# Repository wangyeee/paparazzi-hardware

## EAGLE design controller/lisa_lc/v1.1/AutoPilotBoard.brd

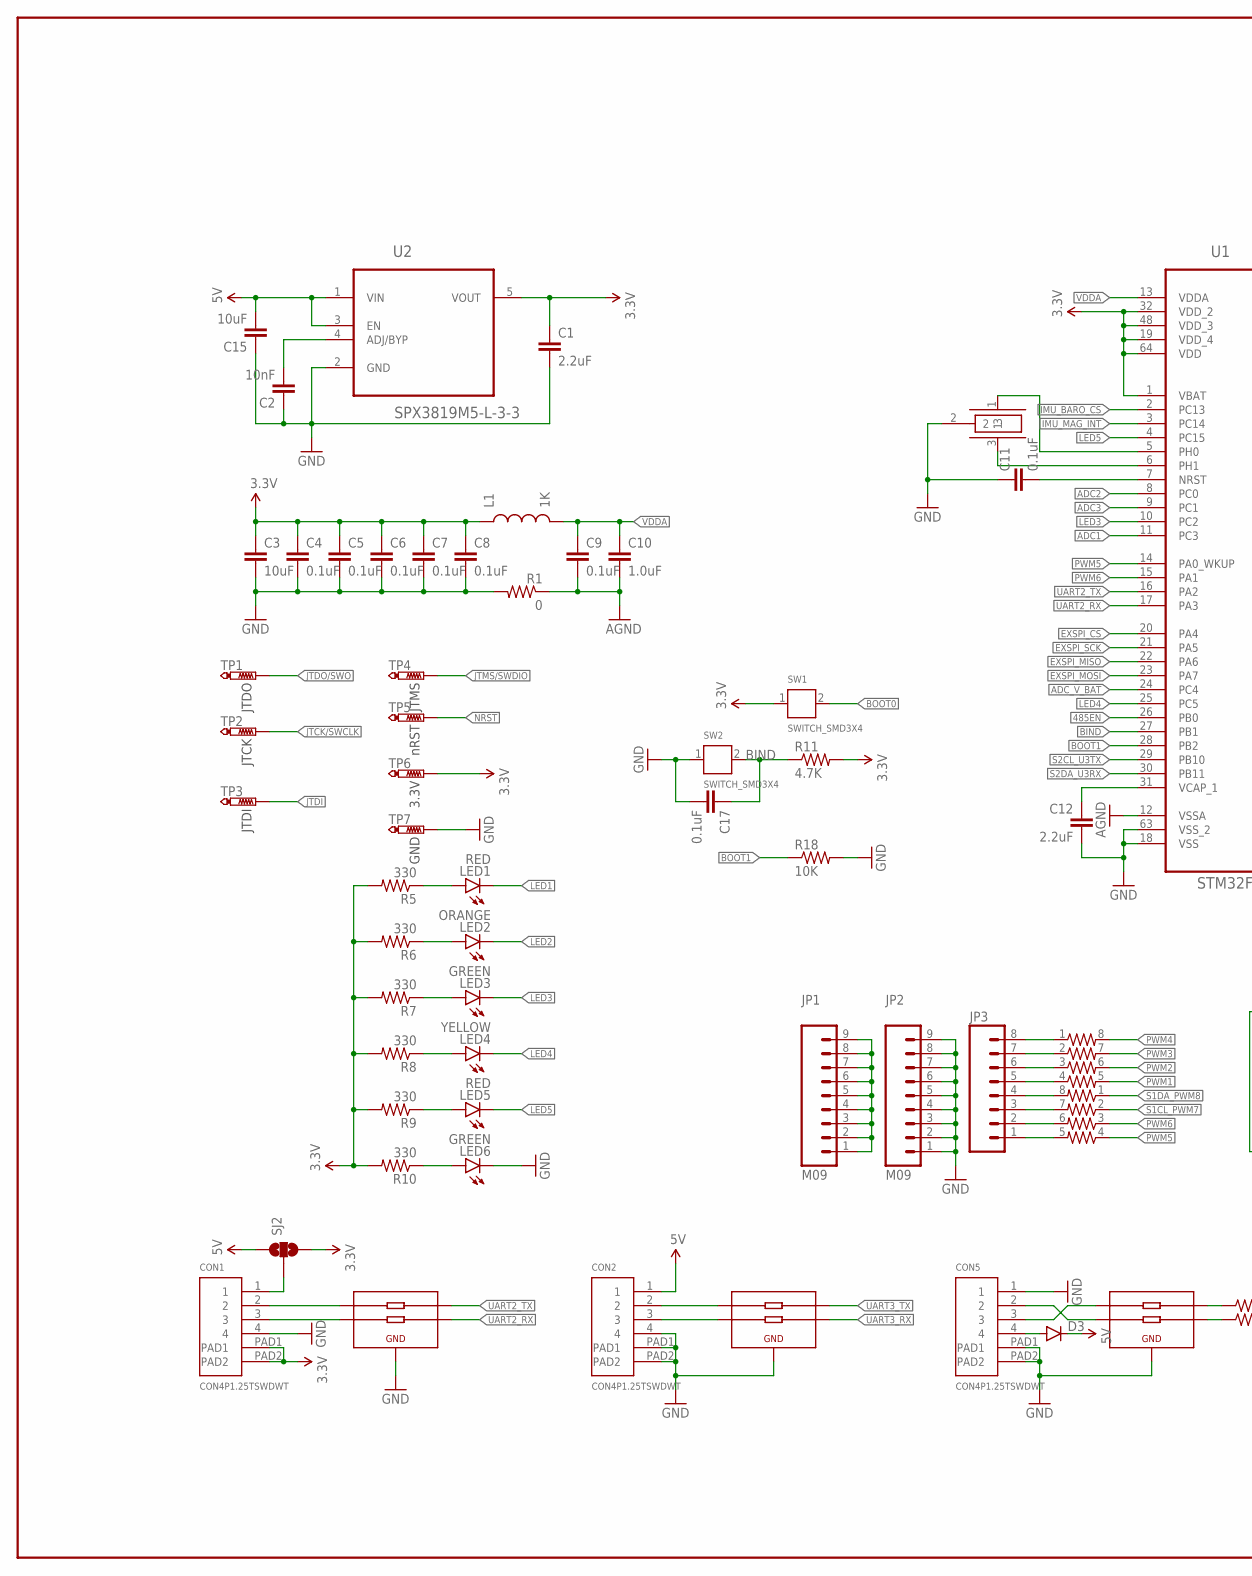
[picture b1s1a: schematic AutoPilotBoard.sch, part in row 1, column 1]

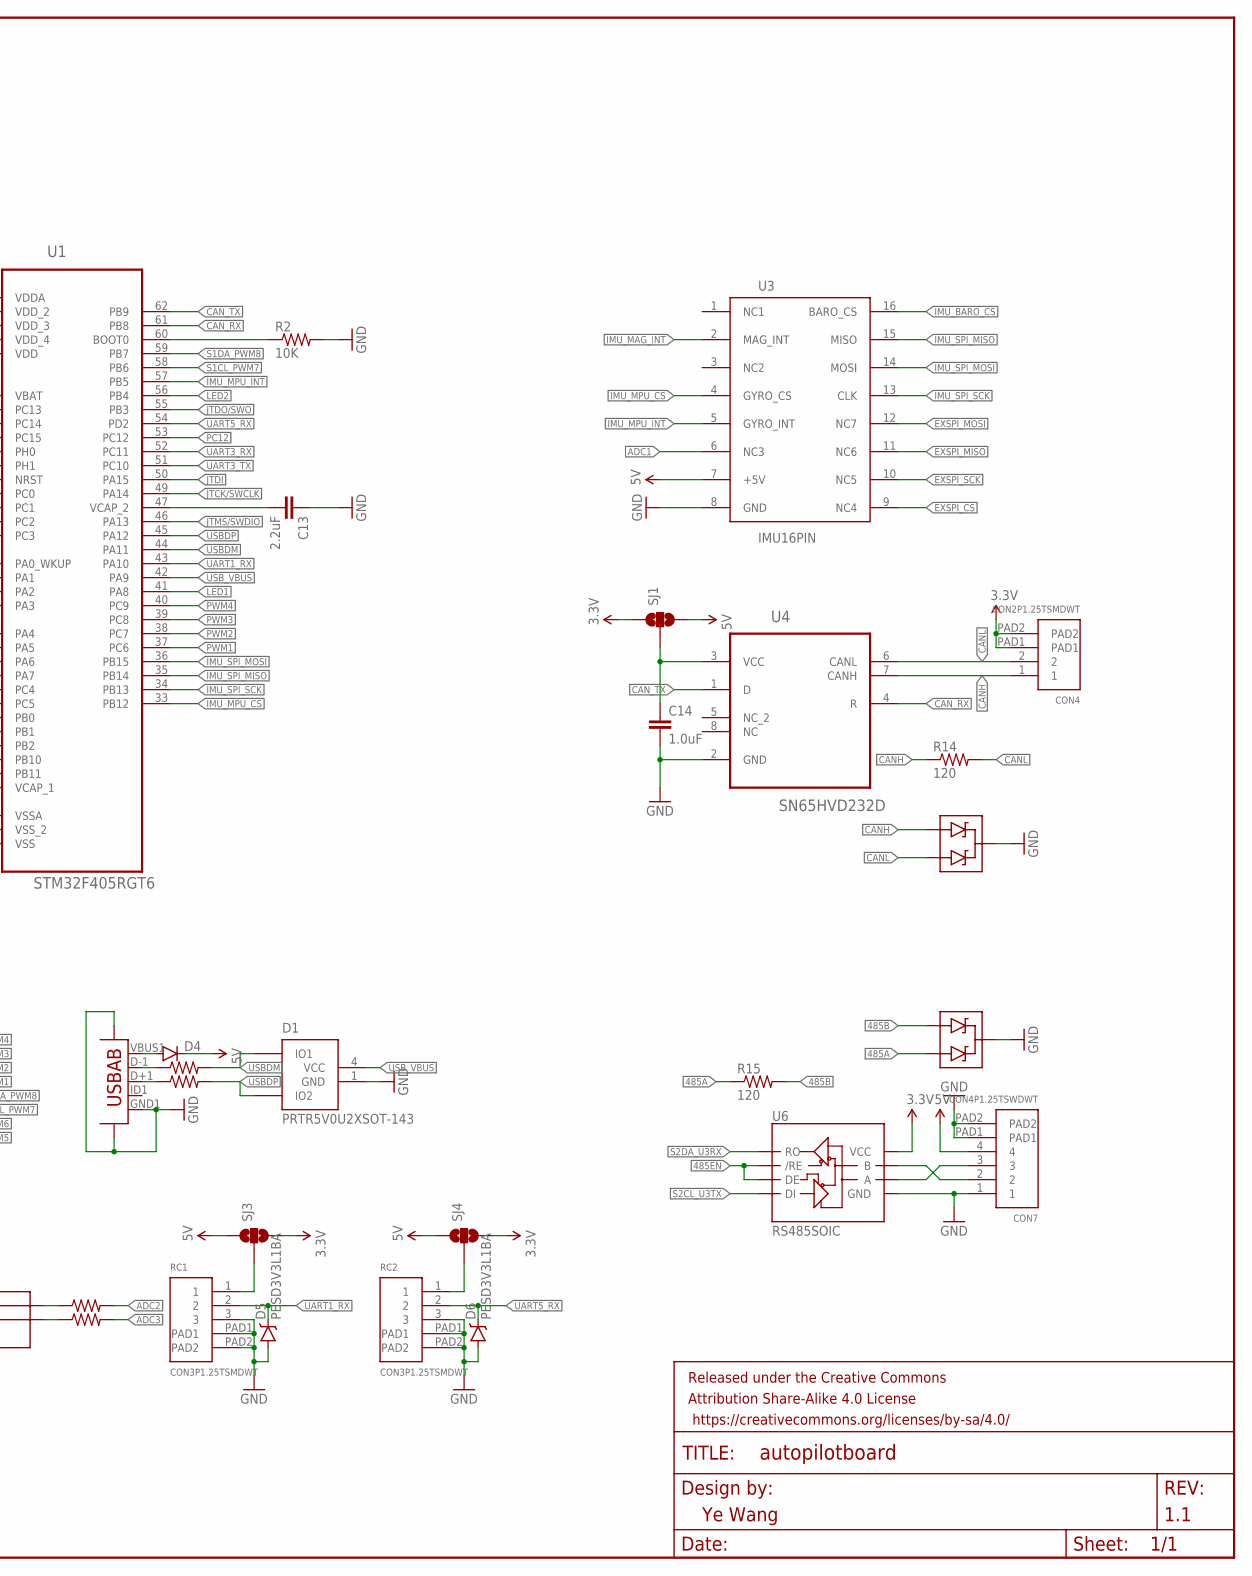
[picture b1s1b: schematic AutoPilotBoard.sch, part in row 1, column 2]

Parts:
C1, C12, C13: 2.2uF; 0603-CAP
C2: 10nF; 0603-CAP
C3: 10uF; 0805-CAP
C4, C5, C6, C7, C8, C9, C11, C17: 0.1uF; 0603-CAP
C10, C14: 1.0uF; 0603-CAP
C15: 10uF; 1206
CON1, CON2, CON5, CON7: CON4P1.25TSWDWT; 1.25T4P
CON4: CON2P1.25TSMDWT; 1.25T2P
D1: PRTR5V0U2XSOT-143; SOT-143B
D2: PESD1CAN; SOT23-3
D3, D4: DIODESOD123; SOD-123
D5, D6: PESD3V3L1BA; SOD-323
D7: SM712; SOT23-3
FIL1, FIL2, FIL3: IP4256CZ5-W; SOT65P210X110-5N
FRAME1: FRAME-LEDGERNO_PKG; DUMMY
JP1, JP2: M09; 1X09
JP3: M08RND; 1X08_ROUND
L1: 1K; 0603
LED1, LED5: RED; LED-0603
LED2: ORANGE; LED-0603
LED3, LED6: GREEN; LED-0603
LED4: YELLOW; LED-0603
R1: 0; 0603-RES
R2, R18: 10K; 0603-RES
R3, R4: 22; 0603-RES
R5, R6, R7, R8, R9, R10: 330; 0603-RES
R11: 4.7K; 0603-RES
R12, R13: 1K; 0603-ARV
R14, R15: 120; 0603-RES
R16, R17: 1K; 0603-RES
RC1, RC2: CON3P1.25TSMDWT; 1.25T3P
SJ1, SJ2, SJ3, SJ4: SOLDERJUMPER_2WAYS; SJ_3
SW1, SW2: SWITCH_SMD3X4; SWITCH3X4_SMD
TP1, TP2, TP3, TP4, TP5, TP6, TP7: PTR1B1,27; B1,27
U1: STM32F405RGT6; QFP50P1200X1200X160-64N
U2: SPX3819M5-L-3-3; SOT95P280X145-5N
U3: IMU16PIN; SMD23X23
U4: SN65HVD232D; SOIC127P600X175-8N
U5: USB-ABCONN-11794; USB-AB-MICRO-SMD_V03
U6: RS485SOIC; SO08
X1: CSTCE8M00G52-R0; CSTCE_M_G

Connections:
3.3V: C1.1, C3.P$1 (1), C4.1, C5.1, C6.1, C7.1, C8.1, CON1.PAD1, CON1.PAD2, CON4.PAD1, CON4.PAD2, L1.1, R5.2, R6.2, R7.2, R8.2, R9.2, R10.2, R11.2, SJ1.1, SJ2.3, SJ3.3, SJ4.3, SW1.1, TP6.TP, U1.1 (VBAT), U1.19 (VDD_4), U1.32 (VDD_2), U1.48 (VDD_3), U1.64 (VDD), U2.5 (VOUT), U6.8 (VCC)
5V: C15.2, CON2.1, CON7.4, D3.C, D4.C, SJ1.3, SJ2.1, SJ3.1, SJ4.1, U2.1 (VIN), U2.3 (EN), U3.7 (+5V)
485A: CON7.3, D7.2 (A2), R15.1, U6.6 (A)
485B: CON7.2, D7.1 (A1), R15.2, U6.7 (B)
485EN: U1.26 (PB0), U6.2 (/RE), U6.3 (DE)
ADC1: U1.11 (PC3), U3.6 (NC3)
ADC2: R16.2, U1.8 (PC0)
ADC3: R17.2, U1.9 (PC1)
ADC_V_BAT: U1.24 (PC4)
AGND: C9.2, C10.2, R1.1, U1.12 (VSSA)
BIND: C17.1, R11.1, SW2.2, U1.27 (PB1)
BOOT0: R2.1, SW1.2, U1.60 (BOOT0)
BOOT1: R18.1, U1.28 (PB2)
CANH: CON4.1, D2.1 (A1), R14.1, U4.7 (CANH)
CANL: CON4.2, D2.2 (A2), R14.2, U4.6 (CANL)
CAN_RX: U1.61 (PB8), U4.4 (R)
CAN_TX: U1.62 (PB9), U4.1 (D)
EXSPI_CS: U1.20 (PA4), U3.9 (NC4)
EXSPI_MISO: U1.22 (PA6), U3.11 (NC6)
EXSPI_MOSI: U1.23 (PA7), U3.12 (NC7)
EXSPI_SCK: U1.21 (PA5), U3.10 (NC5)
GND: C1.2, C2.1, C3.P$2 (2), C4.2, C5.2, C6.2, C7.2, C8.2, C11.1, C12.2, C13.1, C14.2, C15.1, C17.2, CON1.4, CON2.4, CON2.PAD1, CON2.PAD2, CON5.1, CON5.PAD1, CON5.PAD2, CON7.1, CON7.PAD1, CON7.PAD2, D1.1 (GND), D2.3 (C), D5.A, D6.A, D7.3 (C), FIL1.2, FIL2.2, FIL3.2, JP2.1, JP2.2, JP2.3, JP2.4, JP2.5, JP2.6, JP2.7, JP2.8, JP2.9, LED6.C, R1.2, R2.2, R18.2, RC1.3, RC1.PAD1, RC1.PAD2, RC2.3, RC2.PAD1, RC2.PAD2, SW2.1, TP7.TP, U1.18 (VSS), U1.63 (VSS_2), U2.2 (GND), U3.8 (GND), U4.2 (GND), U5.CON1 (SHL1), U5.CON2 (SHL2), U5.GND1 (GND), U6.5 (GND), X1.2
IMU_BARO_CS: U1.2 (PC13), U3.16 (BARO_CS)
IMU_MAG_INT: U1.3 (PC14), U3.2 (MAG_INT)
IMU_MPU_CS: U1.33 (PB12), U3.4 (GYRO_CS)
IMU_MPU_INT: U1.57 (PB5), U3.5 (GYRO_INT)
IMU_SPI_MISO: U1.35 (PB14), U3.15 (MISO)
IMU_SPI_MOSI: U1.36 (PB15), U3.14 (MOSI)
IMU_SPI_SCK: U1.34 (PB13), U3.13 (CLK)
JTCK/SWCLK: TP2.TP, U1.49 (PA14)
JTDI: TP3.TP, U1.50 (PA15)
JTDO/SWO: TP1.TP, U1.55 (PB3)
JTMS/SWDIO: TP4.TP, U1.46 (PA13)
LED1: LED1.C, U1.41 (PA8)
LED2: LED2.C, U1.56 (PB4)
LED3: LED3.C, U1.10 (PC2)
LED4: LED4.C, U1.25 (PC5)
LED5: LED5.C, U1.4 (PC15)
unnamed: C14.1, SJ1.2, U4.3 (VCC)
unnamed: U1.6 (PH1), X1.3
unnamed: C2.2, U2.4 (ADJ/BYP)
unnamed: U1.5 (PH0), X1.1
unnamed: C12.1, U1.31 (VCAP_1)
unnamed: C13.2, U1.47 (VCAP_2)
unnamed: R3.1, U5.D-1 (D-)
unnamed: R4.1, U5.D+1 (D+)
unnamed: LED1.A, R5.1
unnamed: LED3.A, R7.1
unnamed: LED4.A, R8.1
unnamed: LED5.A, R9.1
unnamed: LED2.A, R6.1
unnamed: CON5.3, FIL1.1
unnamed: RC1.1, SJ3.2
unnamed: CON5.2, FIL1.3
unnamed: JP3.5, R12.4 (1)
unnamed: JP3.6, R12.3 (1)
unnamed: JP3.7, R12.2 (1)
unnamed: JP3.8, R12.1
unnamed: JP3.4, R13.8 (2)
unnamed: JP3.3, R13.7 (2)
unnamed: JP3.2, R13.6 (2)
unnamed: LED6.A, R10.1
unnamed: JP3.1, R13.5 (2)
unnamed: FIL1.5, R16.1
unnamed: FIL1.4, R17.1
unnamed: CON1.2, FIL2.1
unnamed: CON1.3, FIL2.3
unnamed: CON2.3, FIL3.4
unnamed: CON2.2, FIL3.5
unnamed: CON5.4, D3.A
unnamed: CON1.1, SJ2.2
unnamed: RC2.1, SJ4.2
NRST: C11.2, TP5.TP, U1.7 (NRST)
PC12: U1.53 (PC12)
PWM1: R12.5 (2), U1.37 (PC6)
PWM2: R12.6 (2), U1.38 (PC7)
PWM3: R12.7 (2), U1.39 (PC8)
PWM4: R12.8 (2), U1.40 (PC9)
PWM5: R13.4 (1), U1.14 (PA0_WKUP)
PWM6: R13.3 (1), U1.15 (PA1)
S1CL_PWM7: R13.2 (1), U1.58 (PB6)
S1DA_PWM8: R13.1, U1.59 (PB7)
S2CL_U3TX: U1.29 (PB10), U6.4 (DI)
S2DA_U3RX: U1.30 (PB11), U6.1 (RO)
SRV_COM: JP1.1, JP1.2, JP1.3, JP1.4, JP1.5, JP1.6, JP1.7, JP1.8, JP1.9
UART1_RX: D5.C, RC1.2, U1.43 (PA10)
UART2_RX: FIL2.4, U1.17 (PA3)
UART2_TX: FIL2.5, U1.16 (PA2)
UART3_RX: FIL3.3, U1.52 (PC11)
UART3_TX: FIL3.1, U1.51 (PC10)
UART5_RX: D6.C, RC2.2, U1.54 (PD2)
USBDM: D1.2 (IO1), R3.2, U1.44 (PA11)
USBDP: D1.3 (IO2), R4.2, U1.45 (PA12)
USB_VBUS: D1.4 (VCC), D4.A, U1.42 (PA9), U5.VBUS1 (VBUS)
VDDA: C9.1, C10.1, L1.2, U1.13 (VDDA)

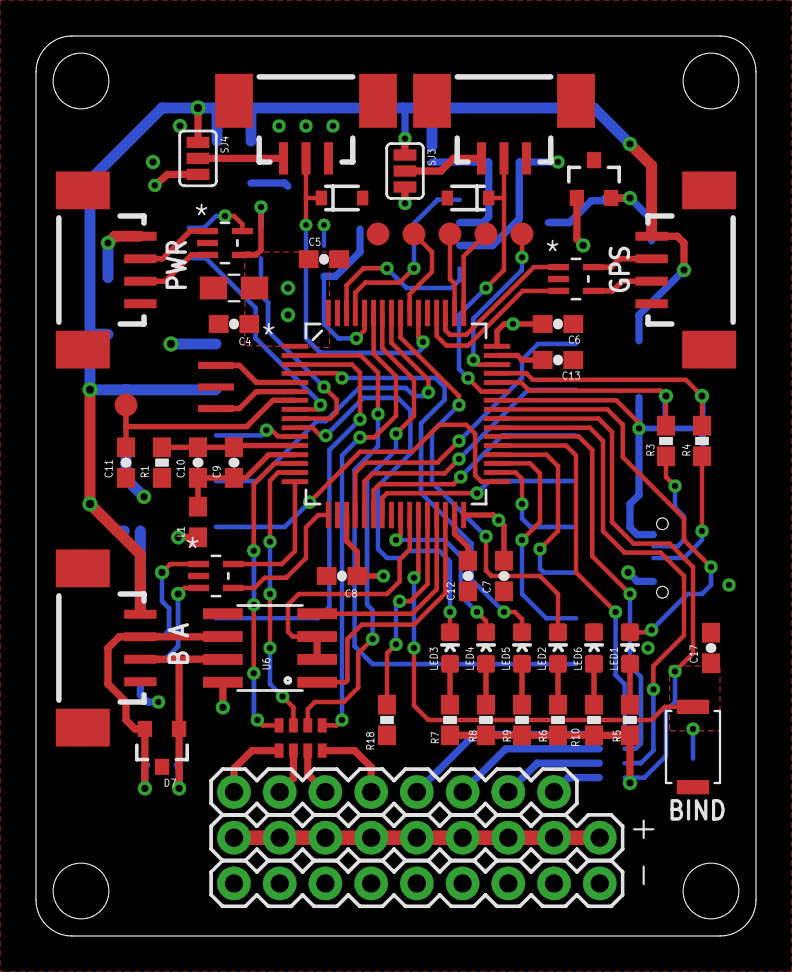
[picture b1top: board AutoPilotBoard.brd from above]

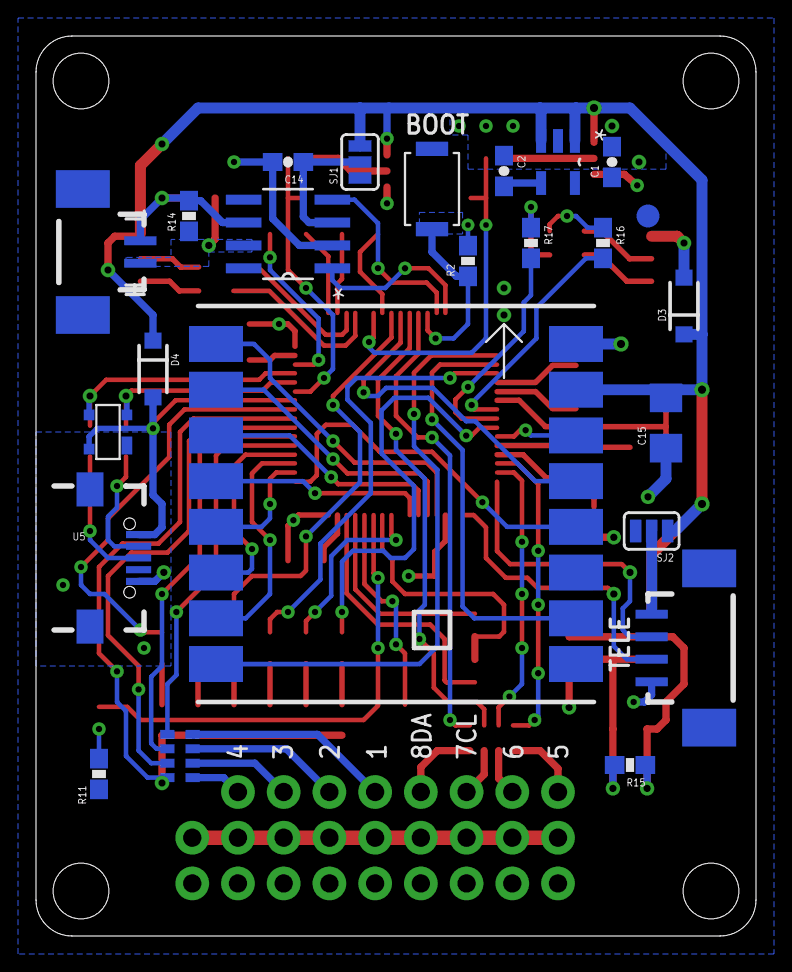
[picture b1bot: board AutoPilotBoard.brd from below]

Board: 2 copper layers, 40.0 x 50.0 mm, 82 parts (24 on the bottom side), 93 nets.

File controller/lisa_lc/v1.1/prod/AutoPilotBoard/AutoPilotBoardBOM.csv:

Part,Value,Package,Description
C1,2.2uF,0603-CAP,Capacitor
C10,1.0uF,0603-CAP,Capacitor
C11,0.1uF,0603-CAP,Capacitor
C12,2.2uF,0603-CAP,Capacitor
C13,2.2uF,0603-CAP,Capacitor
C14,1.0uF,0603-CAP,Capacitor
C15,10uF,1206-CAP,Capacitor
C17,0.1uF,0603-CAP,Capacitor
C2,10nF,0603-CAP,Capacitor
C3,10uF,0805-CAP,Capacitor
C4,0.1uF,0603-CAP,Capacitor
C5,0.1uF,0603-CAP,Capacitor
C6,0.1uF,0603-CAP,Capacitor
C7,0.1uF,0603-CAP,Capacitor
C8,0.1uF,0603-CAP,Capacitor
C9,0.1uF,0603-CAP,Capacitor
CON1,CON4P1.25TSWDWT,1.25T4P,4 Pin 1.25mm SMD Connector
CON2,CON4P1.25TSWDWT,1.25T4P,4 Pin 1.25mm SMD Connector
CON4,CON2P1.25TSMDWT,1.25T2P,4 Pin 1.25mm SMD Connector
CON5,CON4P1.25TSWDWT,1.25T4P,4 Pin 1.25mm SMD Connector
CON7,CON4P1.25TSWDWT,1.25T4P,4 Pin 1.25mm SMD Connector
D1,PRTR5V0U2XSOT-143,SOT-143B,I2C Bus ESD Protection
D2,PESD1CAN,SOT23-3,CAN Bus ESD Protection
D3,MBR0520LT1G,SOD-123,Diode
D4,MBR0520LT1G,SOD-123,Diode
D5,PESD3V3L1BA,SOD-323,Schottky diodes in SFE's production catalog
D6,PESD3V3L1BA,SOD-323,Schottky diodes in SFE's production catalog
D7,SM712,SOT23-3,RS485 Bus ESD protection
FIL1,IP4256CZ5-W,SOT65P210X110-5N,Dual-channel passive filter network with ESD protection
FIL2,IP4256CZ5-W,SOT65P210X110-5N,Dual-channel passive filter network with ESD protection
FIL3,IP4256CZ5-W,SOT65P210X110-5N,Dual-channel passive filter network with ESD protection
JP1,M09,1X09,Header 9
JP2,M09,1X09,Header 9
JP3,M08,1X08_ROUND,Header 8
L1,1K,0603,Inductors
LED1,RED,LED-0603,LED
LED2,ORANGE,LED-0603,LED
LED3,GREEN,LED-0603,LED
LED4,YELLOW,LED-0603,LED
LED5,RED,LED-0603,LED
LED6,GREEN,LED-0603,LED
R1,0,0603-RES,Resistor
R10,330,0603-RES,Resistor
R11,4.7K,0603-RES,Resistor
R12,1K,0603-ARV,Array Chip Resistor
R13,1K,0603-ARV,Array Chip Resistor
R14,120,0603-RES,Resistor
R15,120,0603-RES,Resistor
R16,1K,0603-RES,Resistor
R17,1K,0603-RES,Resistor
R18,10K,0603-RES,Resistor
R2,10K,0603-RES,Resistor
R3,22,0603-RES,Resistor
R4,22,0603-RES,Resistor
R5,330,0603-RES,Resistor
R6,330,0603-RES,Resistor
R7,330,0603-RES,Resistor
R8,330,0603-RES,Resistor
R9,330,0603-RES,Resistor
RC1,CON3P1.25TSMDWT,1.25T3P,3 Pin 1.25mm SMD Connector
RC2,CON3P1.25TSMDWT,1.25T3P,3 Pin 1.25mm SMD Connector
SW1,SWITCH_SMD3X4,SWITCH3X4_SMD,Boot button
SW2,SWITCH_SMD3X4,SWITCH3X4_SMD,Bind button
U1,STM32F405RGT6,LQFP-64PIN,"ARM Cortex M4 MCU with 1MB FLASH, FPU"
U2,SPX3819M5-L-3-3,SOT95P280X145-5N,"500mA, LOW-NOISE LDO VOLTAGE REGULATOR"
U3,IMU16PIN,SMD23X23,IMU
U4,SN65HVD232D,SOIC127P600X175-8N,CAN transceiver
U5,USB-AB CONN,USB-AB-MICRO-SMD_V03,USB AB connector compatible with USB OTG.
U6,RS485SOIC,SOIC8,RS485 transceiver
X1,CSTCE12M0G55-R0,CSTCE_M_G,12MHz resonators with built-in load capacitors.

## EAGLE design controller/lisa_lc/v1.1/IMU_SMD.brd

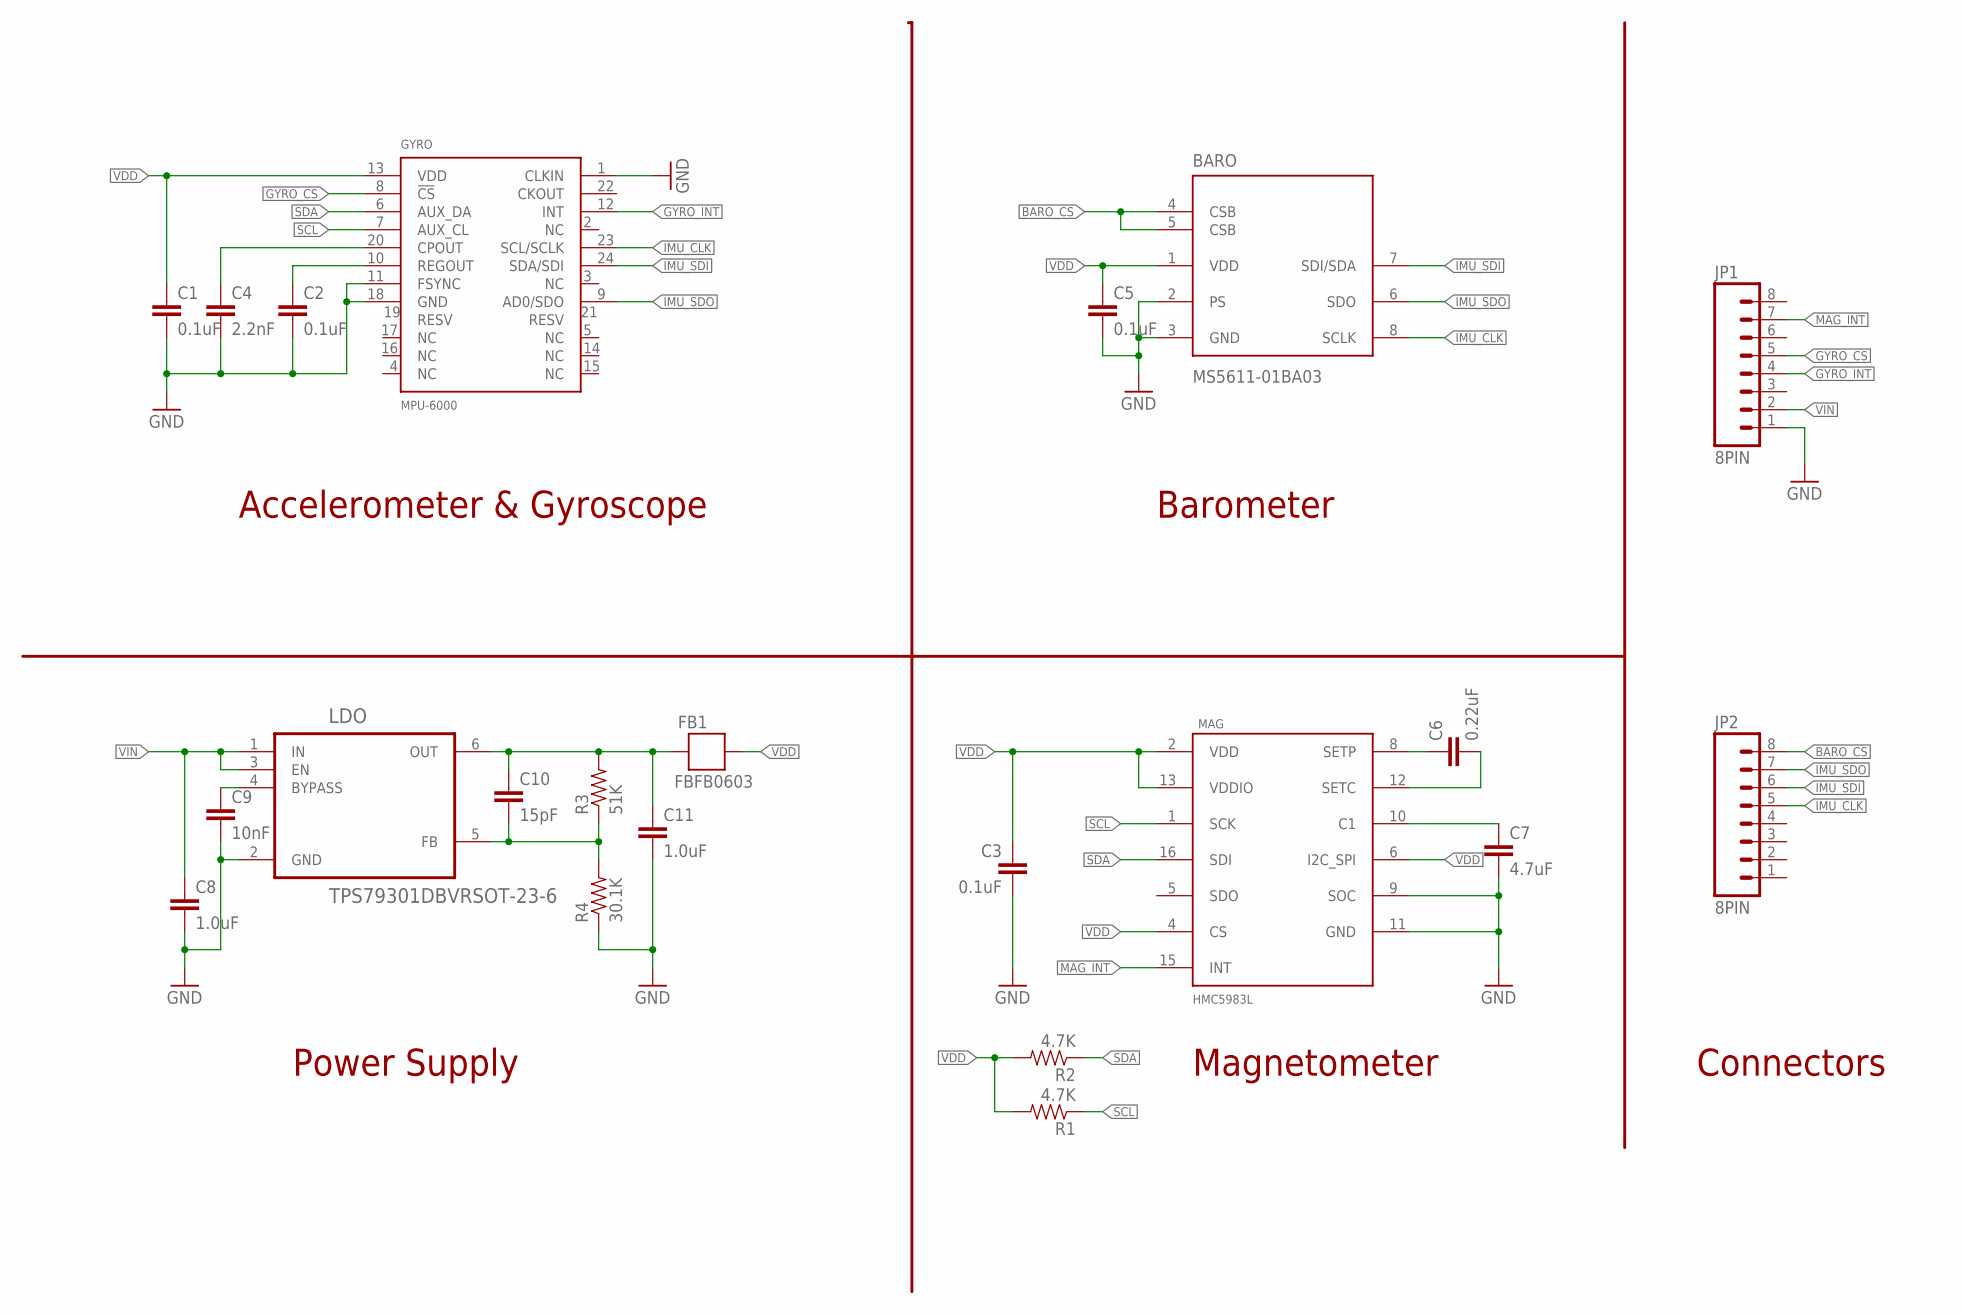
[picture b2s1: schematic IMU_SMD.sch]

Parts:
BARO: MS5611-01BA03; SON125P300X500X100-8N
C1, C2, C3, C5: 0.1uF; 0603-CAP
C4: 2.2nF; 0603-CAP
C6: 0.22uF; 0603-CAP
C7: 4.7uF; 0603-CAP
C8, C11: 1.0uF; 0603-CAP
C9: 10nF; 0603-CAP
C10: 15pF; 0603-CAP
FB1: FBFB0603; 0603
GYRO: MPU-6000; QFN24-NO-PAD
JP1, JP2: 8PIN; 1X08_SQE_NO_SILK
LDO: TPS79301DBVRSOT-23-6; SOT95P280X145-6N
MAG: HMC5983L; LPCC16
R1, R2: 4.7K; 0603-RES
R3: 51K; 0603-RES
R4: 30.1K; 0603-RES

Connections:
BARO_CS: BARO.4 (CSB), BARO.5 (CSB), JP2.8
GND: BARO.2 (PS), BARO.3 (GND), C1.2, C2.2, C3.2, C4.2, C5.2, C7.2, C8.2, C9.2, C11.2, GYRO.1 (CLKIN), GYRO.11 (FSYNC), GYRO.18 (GND), JP1.1, LDO.2 (GND), MAG.9 (SOC), MAG.11 (GND), R4.1
GYRO_CS: GYRO.8 (!CS), JP1.5
GYRO_INT: GYRO.12 (INT), JP1.4
IMU_CLK: BARO.8 (SCLK), GYRO.23 (SCL/SCLK), JP2.5
IMU_SDI: BARO.7 (SDI/SDA), GYRO.24 (SDA/SDI), JP2.6
IMU_SDO: BARO.6 (SDO), GYRO.9 (AD0/SDO), JP2.7
MAG_INT: JP1.7, MAG.15 (INT)
unnamed: C9.1, LDO.4 (BYPASS)
unnamed: C10.1, C11.1, FB1.2, LDO.6 (OUT), R3.2
unnamed: C2.1, GYRO.10 (REGOUT)
unnamed: C4.1, GYRO.20 (CPOUT)
unnamed: C10.2, LDO.5 (FB), R3.1, R4.2
unnamed: C6.1, MAG.8 (SETP)
unnamed: C6.2, MAG.12 (SETC)
unnamed: C7.1, MAG.10 (C1)
SCL: GYRO.7 (AUX_CL), MAG.1 (SCK), R1.1
SDA: GYRO.6 (AUX_DA), MAG.16 (SDI), R2.1
VDD: BARO.1 (VDD), C1.1, C3.1, C5.1, FB1.1, GYRO.13 (VDD), MAG.2 (VDD), MAG.4 (CS), MAG.6 (I2C_SPI), MAG.13 (VDDIO), R1.2, R2.2
VIN: C8.1, JP1.2, LDO.1 (IN), LDO.3 (EN)

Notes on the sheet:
Accelerometer & Gyroscope
Barometer
Power Supply
Magnetometer
Connectors

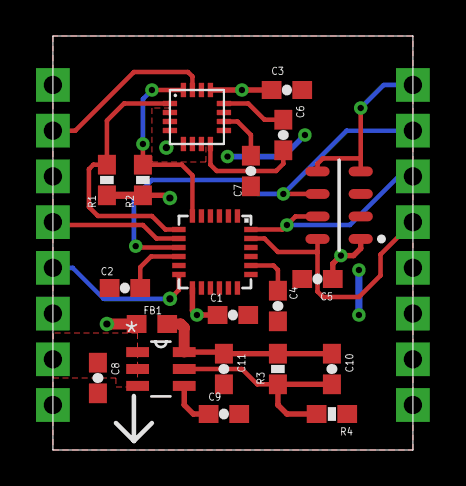
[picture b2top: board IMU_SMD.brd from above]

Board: 2 copper layers, 20.0 x 23.0 mm, 22 parts (0 on the bottom side), 20 nets.

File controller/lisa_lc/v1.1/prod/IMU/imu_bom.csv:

Part,Value,Package,Description
GYRO,MPU-6000,QFN24,3-axis gyroscope and 3-axis accelerometer
BARO,MS5611-01BA03,SON125P-8N,High resolution altimeter sensor
MAG,HMC5983L,LPCC16,Temperature compensated 3-axis magnetometer
LDO,TPS79301DBVR,SOT-23-6,Ultra low noise LDO regulator
C1,0.1uF,0603-CAP,Capacitor
C2,0.1uF,0603-CAP,Capacitor
C3,0.1uF,0603-CAP,Capacitor
C4,2.2nF,0603-CAP,Capacitor
C5,0.1uF,0603-CAP,Capacitor
C6,0.22uF,0603-CAP,Capacitor
C7,4.7uF,0603-CAP,Capacitor
C8,1.0uF,0603-CAP,Capacitor
C9,10nF,0603-CAP,Capacitor
C10,15pF,0603-CAP,Capacitor
C11,1.0uF,0603-CAP,Capacitor
FB1,1K,0603,Ferrite bead
R1,4.7K,0603-RES,Resistor
R2,4.7K,0603-RES,Resistor
R3,51K,0603-RES,Resistor
R4,30.1K,0603-RES,Resistor
JP1,8PIN,1X08_SQE_NO_SILK,Header 8
JP2,8PIN,1X08_SQE_NO_SILK,Header 8

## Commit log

2016-01-18 Source control low cost derivation of LisaMX, a.k.a LisaLC.

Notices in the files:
parts and their libraries:
SparkFun-Retired: Licensing:Creative Commons ShareAlike 4.0 International - https://creativecommons.org/licenses/by-sa/4.0
Volks73-NXPSemiconductors: Creative Commons Attribution-ShareAlike 3.0 Unported (CC BY-SA 3.0), http://creativecommons.org/licenses/by-sa/3.0/.
